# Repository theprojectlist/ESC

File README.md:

# ESC
Low speed ESC board 

We have been looking for a sensored BLDC motor controller for robotics projects, but the existing options are a bit on the pricey side (ODrive etc). We want to build our own 150A capable, compact, slow speed ESC for use in future projects

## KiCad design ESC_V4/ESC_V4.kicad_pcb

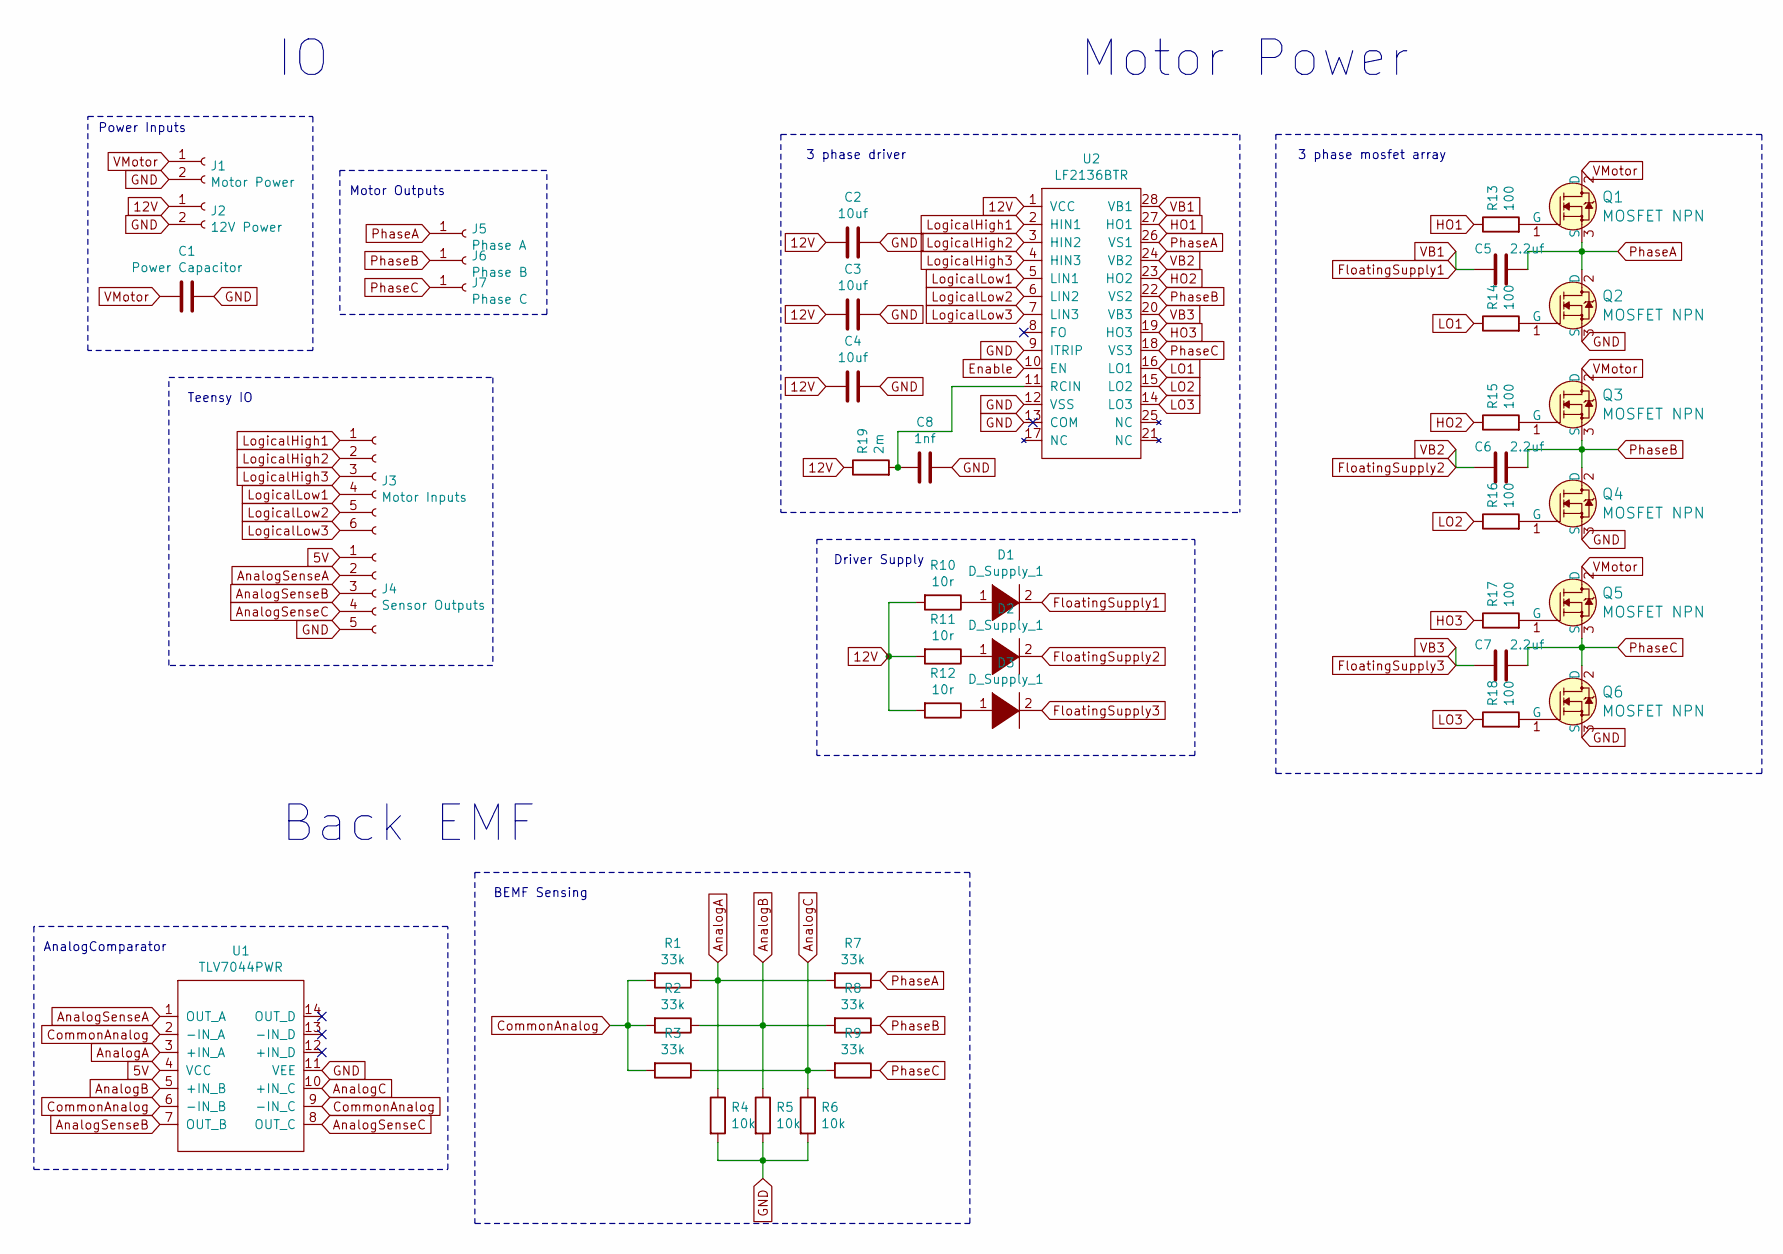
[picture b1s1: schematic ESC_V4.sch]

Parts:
C1: Power Capacitor; C_Elec_10x10.2
C2, C3, C4: 10uf; C_0603_1608Metric
C5, C6, C7: 2.2uf; C_0603_1608Metric
C8: 1nf; C_0603_1608Metric
D1, D2, D3: D_Supply_1; D_SOD-323F
J1: Motor Power; AMASS_XT60-M
J2: 12V Power; PinHeader_1x02_P2.54mm_Vertical
J3: Motor Inputs; PinHeader_1x06_P2.54mm_Vertical
J4: Sensor Outputs; PinHeader_1x05_P2.54mm_Vertical
J5: Phase A; SquarePad4x4
J6: Phase B; SquarePad4x4
J7: Phase C; SquarePad4x4
Q1, Q2, Q3, Q4, Q5, Q6: MOSFET NPN; TO-252-2; MPN IRLB8721PBF; Digi-Key_PN IRLB8721PBF-ND
R1, R2, R3, R7, R8, R9: 33k; R_0603_1608Metric
R4, R5, R6: 10k; R_0603_1608Metric
R10, R11, R12: 10r; R_0603_1608Metric
R13, R14, R15, R16, R17, R18: 100; R_0603_1608Metric
R19: 2m; R_0603_1608Metric
U1: TLV7044PWR; TSSOP-14_4.4x5mm_P0.65mm
U2: LF2136BTR; SOIC-28W_7.5x17.9mm_P1.27mm

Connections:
12V: C2.2, C3.2, C4.2, J2.1, R10.2, R11.2, R12.2, R19.1, U2.1 (VCC)
AnalogA: R1.1, R4.1, R7.2, U1.3 (+IN_A)
AnalogB: R2.1, R5.1, R8.2, U1.5 (+IN_B)
AnalogC: R3.1, R6.1, R9.2, U1.10 (+IN_C)
AnalogSenseA: J4.2, U1.1 (OUT_A)
AnalogSenseB: J4.3, U1.7 (OUT_B)
AnalogSenseC: J4.4, U1.8 (OUT_C)
CommonAnalog: R1.2, R2.2, R3.2, U1.2 (-IN_A), U1.6 (-IN_B), U1.9 (-IN_C)
FloatingSupply1: C5.1, D1.2 (A), U2.28 (VB1)
FloatingSupply2: C6.1, D2.2 (A), U2.24 (VB2)
FloatingSupply3: C7.1, D3.2 (A), U2.20 (VB3)
GND: C1.1, C2.1, C3.1, C4.1, C8.2, J1.2, J2.2, J4.5, Q2.3 (S), Q4.3 (S), Q6.3 (S), R4.2, R5.2, R6.2, U1.11 (VEE), U2.9 (ITRIP), U2.12 (VSS), U2.13 (COM)
HO1: R13.1, U2.27 (HO1)
HO2: R15.1, U2.23 (HO2)
HO3: R17.1, U2.19 (HO3)
LO1: R14.1, U2.16 (LO1)
LO2: R16.1, U2.15 (LO2)
LO3: R18.1, U2.14 (LO3)
LogicalHigh1: J3.1, U2.2 (HIN1)
LogicalHigh2: J3.2, U2.3 (HIN2)
LogicalHigh3: J3.3, U2.4 (HIN3)
LogicalLow1: J3.4, U2.5 (LIN1)
LogicalLow2: J3.5, U2.6 (LIN2)
LogicalLow3: J3.6, U2.7 (LIN3)
unnamed: C8.1, R19.2, U2.11 (RCIN)
unnamed: D1.1 (K), R10.1
unnamed: D2.1 (K), R11.1
unnamed: D3.1 (K), R12.1
unnamed: Q1.1 (G), R13.2
unnamed: Q2.1 (G), R14.2
unnamed: Q3.1 (G), R15.2
unnamed: Q4.1 (G), R16.2
unnamed: Q5.1 (G), R17.2
unnamed: Q6.1 (G), R18.2
PhaseA: C5.2, J5.1, Q1.3 (S), Q2.2 (D), R7.1, U2.26 (VS1)
PhaseB: C6.2, J6.1, Q3.3 (S), Q4.2 (D), R8.1, U2.22 (VS2)
PhaseC: C7.2, J7.1, Q5.3 (S), Q6.2 (D), R9.1, U2.18 (VS3)
VMotor: C1.2, J1.1, Q1.2 (D), Q3.2 (D), Q5.2 (D)

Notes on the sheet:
Motor Outputs
3 phase driver
BEMF Sensing
AnalogComparator
Teensy IO
Power Inputs
Back EMF
Motor Power
3 phase mosfet array
Driver Supply

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
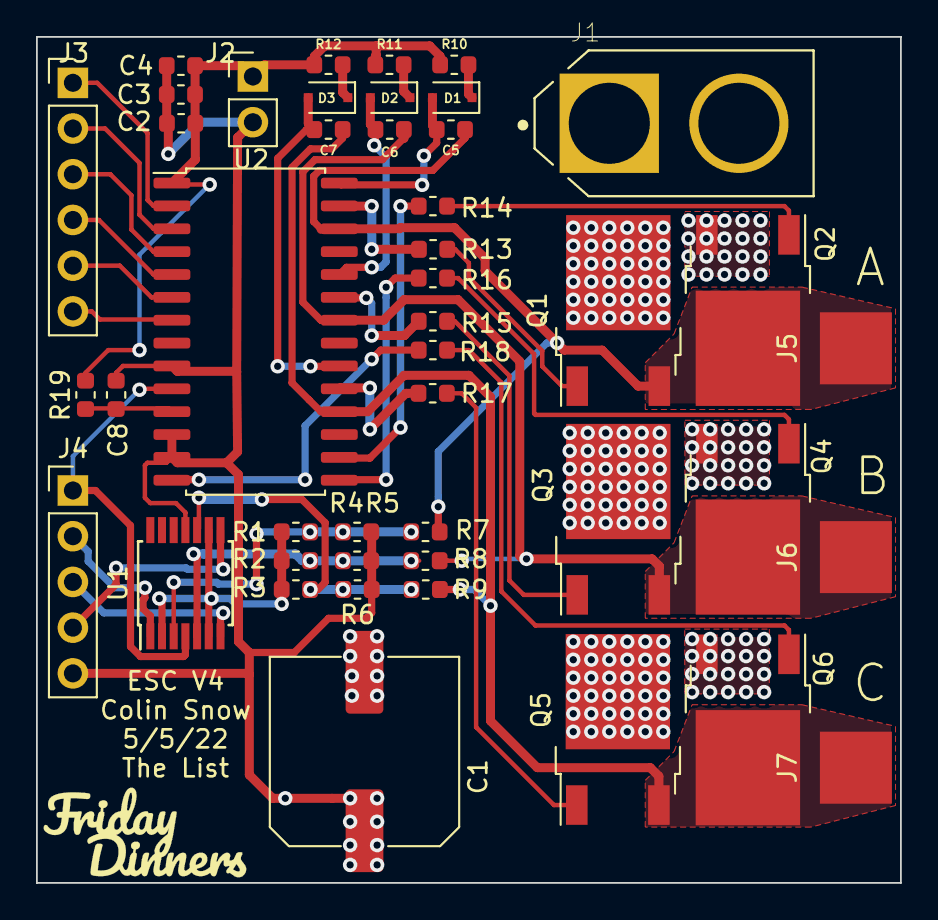
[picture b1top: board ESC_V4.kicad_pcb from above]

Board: 2 copper layers, 48.0 x 47.0 mm, 45 parts (0 on the bottom side), 39 nets.

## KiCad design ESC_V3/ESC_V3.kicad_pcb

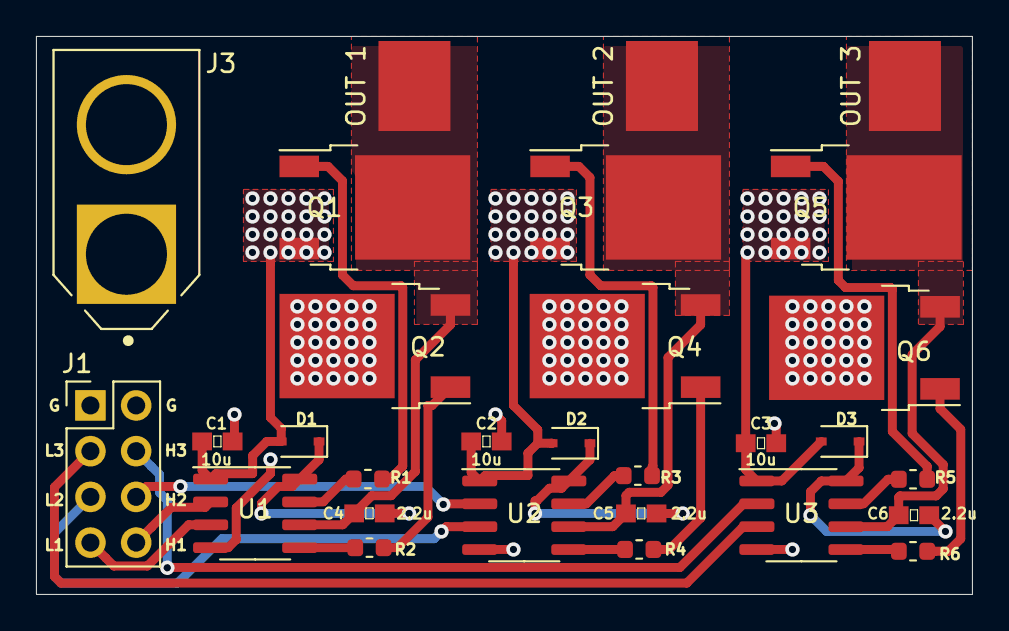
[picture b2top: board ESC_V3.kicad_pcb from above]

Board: 2 copper layers, 52.0 x 31.0 mm, 29 parts (0 on the bottom side), 26 nets.

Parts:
C1, C2, C3: 10u; 0603
C4, C5, C6: 2.2u; 0603
D1, D2, D3: 1N4148WS; D_SOD-323
J1: Conn_01x08_Male; PinHeader_2x04_P2.54mm_Vertical
J3: Conn_01x02_Male; AMASS_XT60-M
OUT 1, OUT 2, OUT 3: Conn_01x01_Male; 3 solder pad
Q1, Q2, Q3, Q4, Q5, Q6: MOSFET-NCH-2N7002PW; TO-252-2
R1, R2, R3, R4, R5, R6: 100; R_0603_1608Metric
U1, U2, U3: IR2101; SOIC-8_3.9x4.9mm_P1.27mm

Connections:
GND: C1.2, C2.2, C3.2, J1.1, J1.2, J3.1, Q2.2, Q4.2, Q6.2, U1.4, U2.4, U3.4
H1: J1.8, U1.2
H2: J1.6, U2.2
H3: J1.4, U3.2
L1: J1.7, U1.3
L2: J1.5, U2.3
L3: J1.3, U3.3
unnamed: C4.1, D1.1, U1.8
unnamed: C5.1, D2.1, U2.8
unnamed: C6.1, D3.1, U3.8
unnamed: Q1.1, R1.1
unnamed: Q2.1, R2.1
unnamed: Q3.1, R3.1
unnamed: Q4.1, R4.1
unnamed: Q5.1, R5.1
unnamed: Q6.1, R6.1
unnamed: R1.2, U1.7
unnamed: R2.2, U1.5
unnamed: R3.2, U2.7
unnamed: R4.2, U2.5
unnamed: R5.2, U3.7
unnamed: R6.2, U3.5
OUT1: C4.2, OUT 1.1, Q1.2, Q2.3, U1.6
OUT2: C5.2, OUT 2.1, Q3.2, Q4.3, U2.6
OUT3: C6.2, OUT 3.1, Q5.2, Q6.3, U3.6
VCC: C1.1, C2.1, C3.1, D1.2, D2.2, D3.2, J3.2, Q1.3, Q3.3, Q5.3, U1.1, U2.1, U3.1

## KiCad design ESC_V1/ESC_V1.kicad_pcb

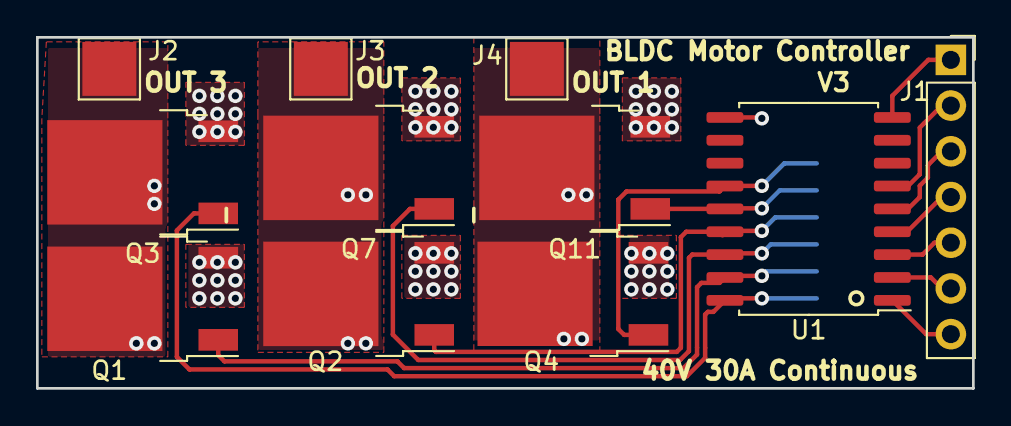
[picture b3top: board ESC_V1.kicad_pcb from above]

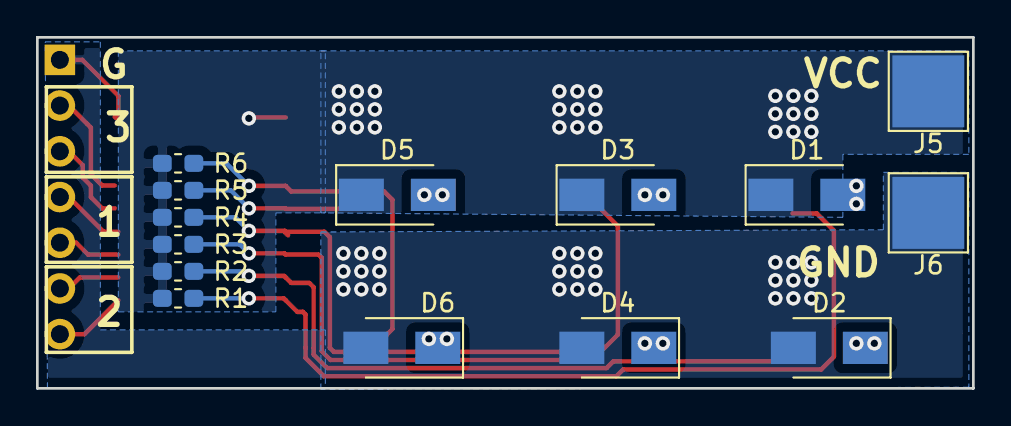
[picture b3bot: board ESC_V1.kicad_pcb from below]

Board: 2 copper layers, 52.0 x 19.5 mm, 25 parts (14 on the bottom side), 17 nets.

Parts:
D1, D2, D3, D4, D5, D6: D; D_SMA
J1: Conn_01x07_Female; PinSocket_1x07_P2.54mm_Vertical
J2, J3, J4: Conn_01x01_Female; TestPoint_Pad_3.0x3.0mm
J5, J6: Conn_01x01_Female; TestPoint_Pad_4.0x4.0mm
Q1, Q2, Q4: BSP129; TO-252-2
Q3, Q7, Q11: P Channel 40V 30A; TO-252-2
R1, R2, R3, R4, R5, R6: 100 ohm; R_0603_1608Metric_Pad1.05x0.95mm_HandSolder
U1: ULN2803A; SOIC-18W_7.5x11.6mm_P1.27mm

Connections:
GND: D2.2, D4.2, D6.2, J1.1, J6.1, Q1.3, Q2.3, Q4.3, U1.9
MOTOR1: D1.2, D2.1, J2.1, Q1.2, Q3.2
MOTOR2: D3.2, D4.1, J3.1, Q2.2, Q7.2
MOTOR3: D5.2, D6.1, J4.1, Q4.2, Q11.2
unnamed: J1.2, U1.6
unnamed: J1.3, U1.5
unnamed: J1.4, U1.4
unnamed: J1.5, U1.3
unnamed: J1.6, U1.2
unnamed: J1.7, U1.1
OUT1: Q3.1, R1.2, U1.18
OUT2: Q1.1, R2.2, U1.17
OUT3: Q7.1, R3.2, U1.16
OUT4: Q2.1, R4.2, U1.15
OUT5: Q11.1, R5.2, U1.14
OUT6: Q4.1, R6.2, U1.13
VCC: D1.1, D3.1, D5.1, J5.1, Q3.3, Q7.3, Q11.3, R1.1, R2.1, R3.1, R4.1, R5.1, R6.1, U1.10

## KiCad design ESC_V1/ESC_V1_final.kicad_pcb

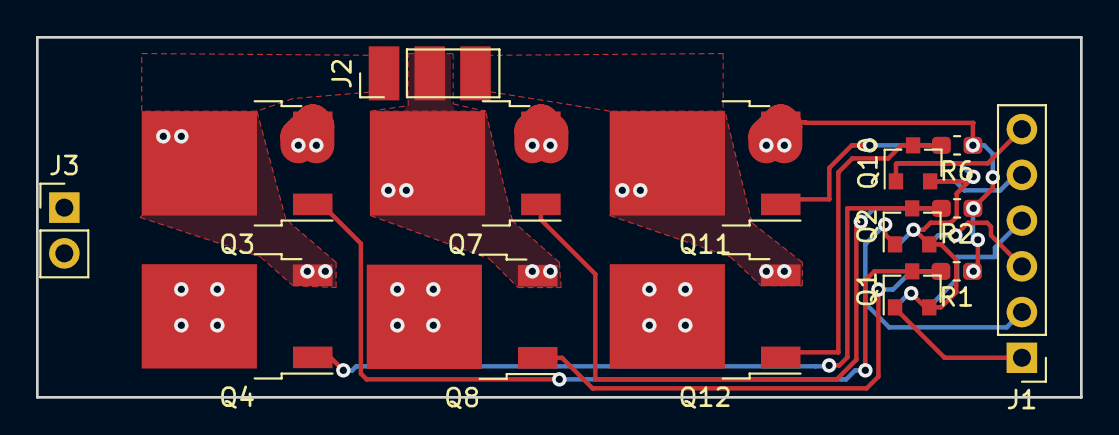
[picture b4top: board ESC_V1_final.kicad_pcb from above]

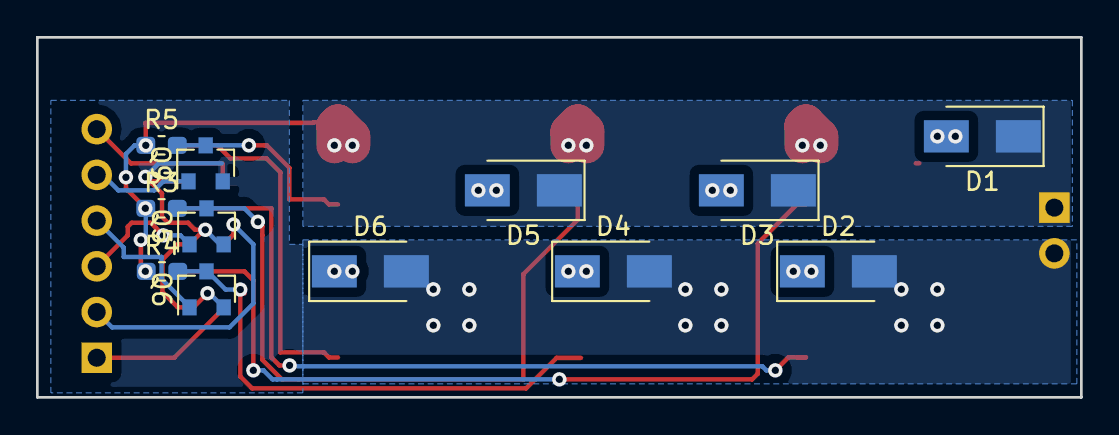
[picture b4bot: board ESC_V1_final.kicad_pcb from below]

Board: 2 copper layers, 58.0 x 20.0 mm, 27 parts (12 on the bottom side), 17 nets.

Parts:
D1, D2, D3, D4, D5, D6: D; D_SMA
J1: Conn_01x06_Female; PinHeader_1x06_P2.54mm_Vertical
J2: Conn_01x03_Female; PinHeader_1x03_P2.54mm_Vertical
J3: Conn_01x02_Female; PinHeader_1x02_P2.54mm_Vertical
Q1, Q2, Q5, Q6, Q9, Q10: NPN Transistor 40V; SOT-23
Q3, Q7, Q11: P Channel 40V 30A; TO-252-2
Q4, Q8, Q12: N Channel 40V 30A; TO-252-2
R1, R2, R3, R4, R5, R6: 10k; R_0603_1608Metric_Pad1.05x0.95mm_HandSolder

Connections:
GND: D2.2, D4.2, D6.2, J3.2, Q1.2, Q2.2, Q4.2, Q5.2, Q6.2, Q8.2, Q9.2, Q10.2, Q12.2
IN1: J1.1, Q1.1
IN2: J1.2, Q2.1
IN3: J1.3, Q5.1
IN4: J1.4, Q6.1
IN5: J1.5, Q9.1
IN6: J1.6, Q10.1
unnamed: Q1.3, Q3.1, R1.2
unnamed: Q2.3, Q4.1, R2.2
unnamed: Q5.3, Q7.1, R3.2
unnamed: Q6.3, Q8.1, R4.2
unnamed: Q10.3, Q12.1, R6.2
unnamed: Q9.3, Q11.1, R5.2
OUT1: D1.2, D2.1, J2.1, Q3.2, Q4.3
OUT2: D3.2, D4.1, J2.2, Q7.2, Q8.3
OUT3: D5.2, D6.1, J2.3, Q11.2, Q12.3
VCC: D1.1, D3.1, D5.1, J3.1, Q3.3, Q7.3, Q11.3, R1.1, R2.1, R3.1, R4.1, R5.1, R6.1

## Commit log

2020-02-12 V1 board
2020-02-12 Board v2 with darlington array and higher current capacity
2020-02-27 Board before redesign
2020-02-27 FETs moved but no bridge drivers yet
2020-04-11 Fixing git issues
2021-08-12 First pass version 3
2021-08-12 Remap input pins to not be terrible
2021-08-14 minor cleanup
2022-03-05 Schematic for version 4
2022-03-05 Footprint associations
2022-03-05 Add components to driver and small tweaks
2022-03-05 Start of pcb layout
2022-03-05 Starting routing, not super happy about positions
2022-03-05 initial routing
2022-03-05 Fix enable connection
2022-03-05 Potentially finished layout
2022-03-06 Potentially finished board
2022-03-06 Gerber files written and board ordered
